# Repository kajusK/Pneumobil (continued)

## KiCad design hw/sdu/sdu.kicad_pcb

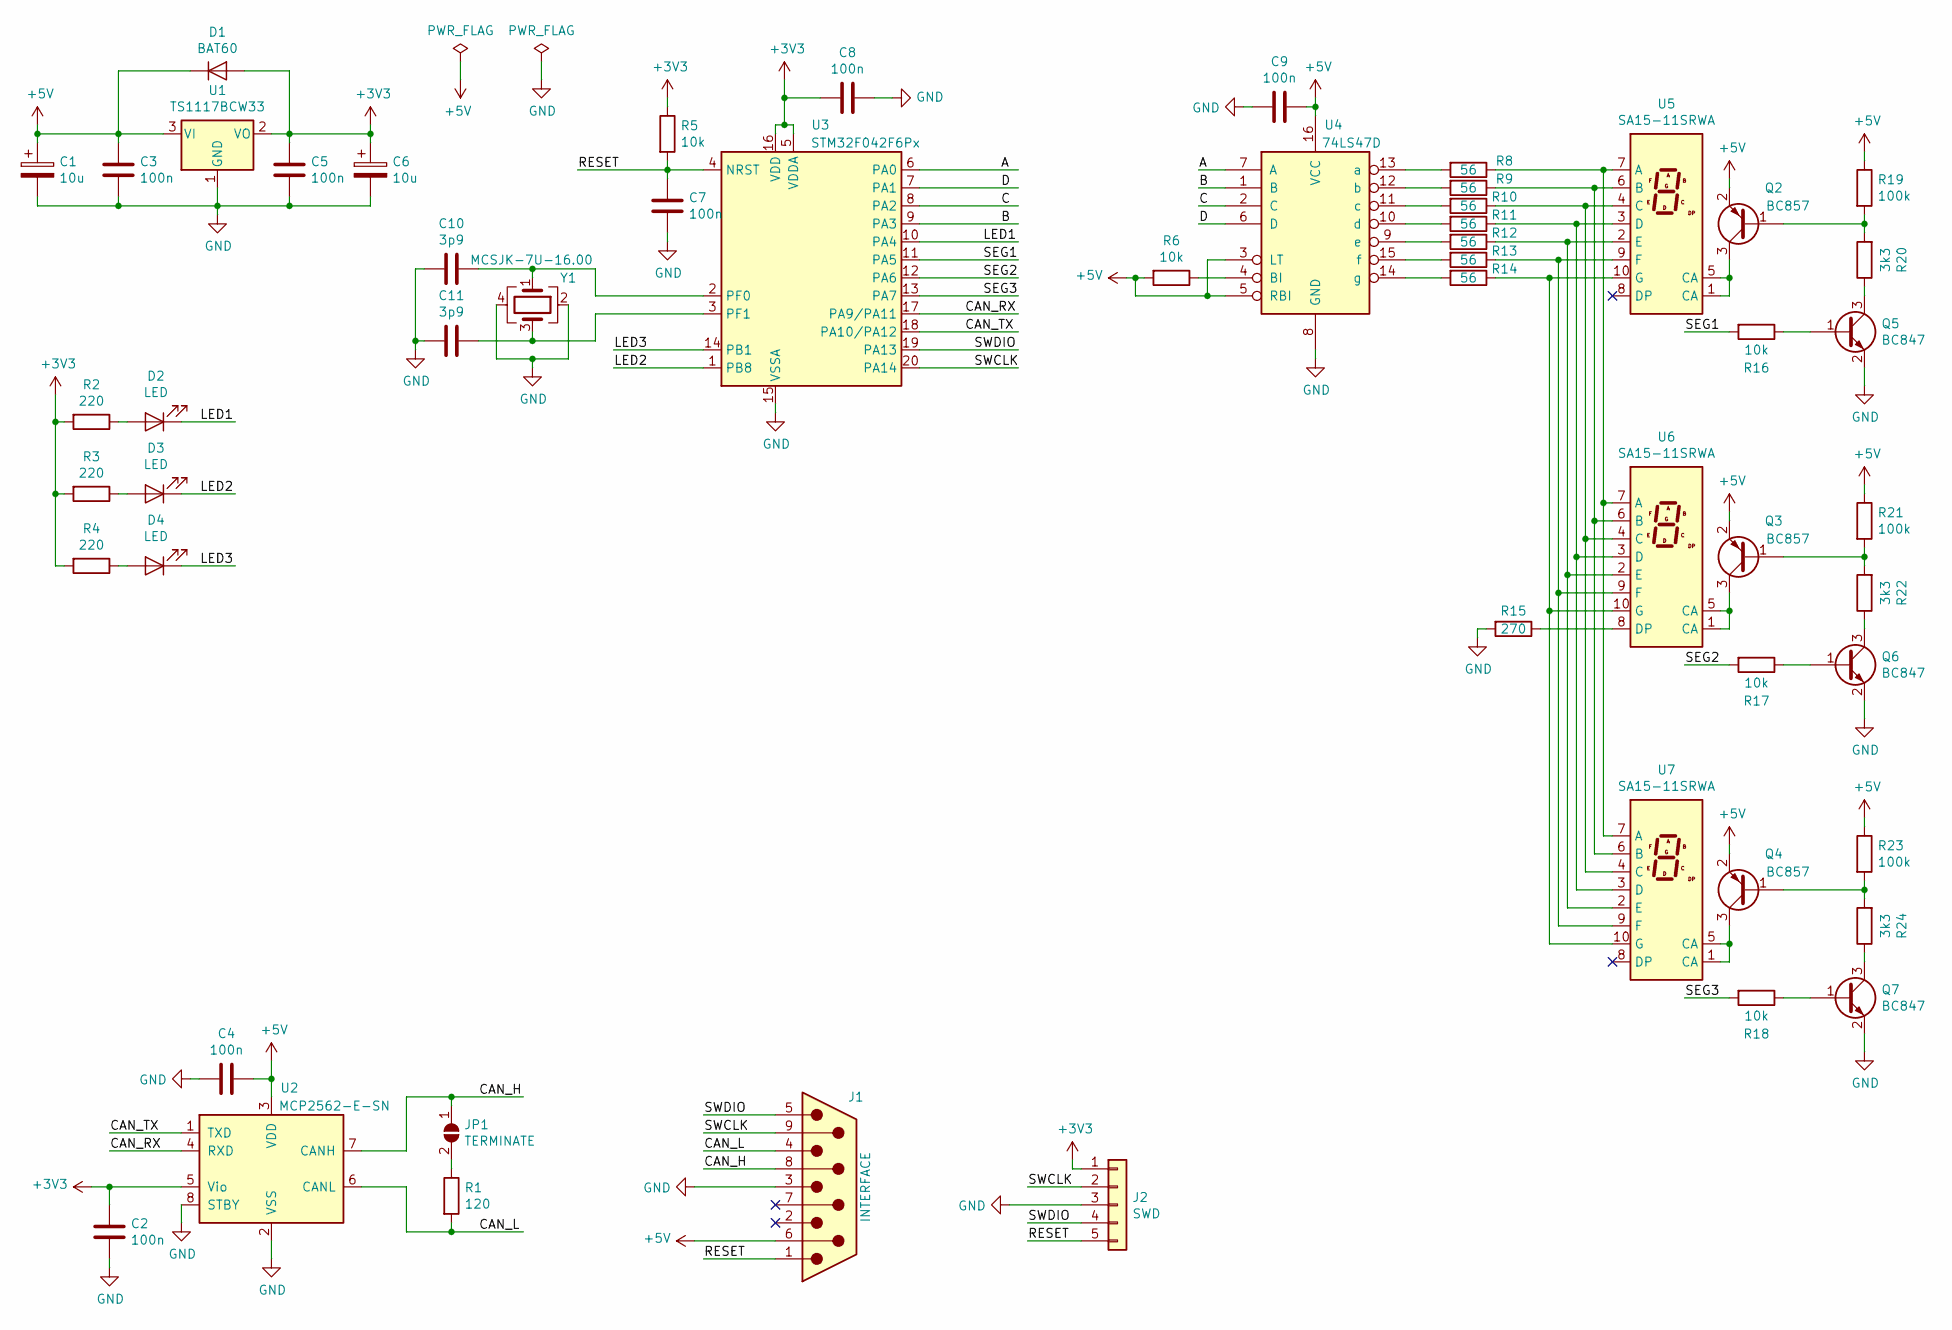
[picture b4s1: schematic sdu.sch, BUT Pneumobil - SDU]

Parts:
C1, C6: 10u; C_0805_2012Metric
C2, C3, C4, C5, C7, C8, C9: 100n; C_0805_2012Metric
C10, C11: 3p9; C_0805_2012Metric
D1: BAT60; D_SOD-323
D2, D3, D4: LED; LED_D5.0mm
J1: INTERFACE; DSUB-9_Female_Vertical_P2.77x2.84mm_MountingHoles
J2: SWD; PinHeader_1x05_P2.54mm_Horizontal
JP1: TERMINATE; SolderJumper-2_P1.3mm_Open_TrianglePad1.0x1.5mm
Q2, Q3, Q4: BC857; SOT-23
Q5, Q6, Q7: BC847; SOT-23
R1: 120; R_0805_2012Metric
R2, R3, R4: 220; R_0805_2012Metric
R5, R6, R16, R17, R18: 10k; R_0805_2012Metric
R8, R9, R10, R11, R12, R13, R14: 56; R_0805_2012Metric
R15: 270; R_0805_2012Metric
R19, R21, R23: 100k; R_0805_2012Metric
R20, R22, R24: 3k3; R_0805_2012Metric
U1: TS1117BCW33; SOT-223-3_TabPin2
U2: MCP2562-E-SN; SOIC-8_3.9x4.9mm_P1.27mm
U3: STM32F042F6Px; TSSOP-20_4.4x6.5mm_P0.65mm
U4: 74LS47D; SOIC-16_3.9x9.9mm_P1.27mm
U5, U6, U7: SA15-11SRWA; SA15-11
Y1: MCSJK-7U-16.00; Crystal_SMD_3225-4Pin_3.2x2.5mm

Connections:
+3V3: C2.1, C5.1, C6.1, C8.2, D1.2 (A), J2.1, R2.2, R3.2, R4.2, R5.1, U1.2 (VO), U2.5 (Vio), U3.5 (VDDA), U3.16 (VDD)
+5V: C1.1, C3.1, C4.1, C9.1, D1.1 (K), J1.6, Q2.2 (E), Q3.2 (E), Q4.2 (E), R6.2, R19.1, R21.1, R23.1, U1.3 (VI), U2.3 (VDD), U4.3 (LT), U4.5 (RBI), U4.16 (VCC)
/A: U3.6 (PA0), U4.7 (A)
/B: U3.9 (PA3), U4.1 (B)
/C: U3.8 (PA2), U4.2 (C)
/CAN_H: J1.8, JP1.1 (A), U2.7 (CANH)
/CAN_L: J1.4, R1.2, U2.6 (CANL)
/CAN_RX: U2.4 (RXD), U3.17 (PA9/PA11)
/CAN_TX: U2.1 (TXD), U3.18 (PA10/PA12)
/D: U3.7 (PA1), U4.6 (D)
/LED1: D2.1 (K), U3.10 (PA4)
/LED2: D3.1 (K), U3.1 (PB8)
/LED3: D4.1 (K), U3.14 (PB1)
/RESET: C7.1, J1.1, J2.5, R5.2, U3.4 (NRST)
/SEG1: R16.2, U3.11 (PA5)
/SEG2: R17.2, U3.12 (PA6)
/SEG3: R18.2, U3.13 (PA7)
/SWCLK: J1.9, J2.2, U3.20 (PA14)
/SWDIO: J1.5, J2.4, U3.19 (PA13)
GND: C1.2, C2.2, C3.2, C4.2, C5.2, C6.2, C7.2, C8.1, C9.2, C10.2, C11.2, J1.3, J2.3, Q5.2 (E), Q6.2 (E), Q7.2 (E), R15.2, U1.1 (GND), U2.2 (VSS), U2.8 (STBY), U3.15 (VSSA), U4.8 (GND), Y1.2, Y1.4
unnamed: C10.1, U3.2 (PF0), Y1.1
unnamed: C11.1, U3.3 (PF1), Y1.3
unnamed: D2.2 (A), R2.1
unnamed: D3.2 (A), R3.1
unnamed: D4.2 (A), R4.1
unnamed: JP1.2 (B), R1.1
unnamed: Q2.1 (B), R19.2, R20.2
unnamed: Q2.3 (C), U5.1 (CA), U5.5 (CA)
unnamed: Q3.1 (B), R21.2, R22.2
unnamed: Q3.3 (C), U6.1 (CA), U6.5 (CA)
unnamed: Q4.1 (B), R23.2, R24.2
unnamed: Q4.3 (C), U7.1 (CA), U7.5 (CA)
unnamed: Q5.1 (B), R16.1
unnamed: Q5.3 (C), R20.1
unnamed: Q6.1 (B), R17.1
unnamed: Q6.3 (C), R22.1
unnamed: Q7.1 (B), R18.1
unnamed: Q7.3 (C), R24.1
unnamed: R6.1, U4.4 (BI)
unnamed: R8.1, U5.7 (A), U6.7 (A), U7.7 (A)
unnamed: R8.2, U4.13 (a)
unnamed: R9.1, U5.6 (B), U6.6 (B), U7.6 (B)
unnamed: R9.2, U4.12 (b)
unnamed: R10.1, U5.4 (C), U6.4 (C), U7.4 (C)
unnamed: R10.2, U4.11 (c)
unnamed: R11.1, U5.3 (D), U6.3 (D), U7.3 (D)
unnamed: R11.2, U4.10 (d)
unnamed: R12.1, U5.2 (E), U6.2 (E), U7.2 (E)
unnamed: R12.2, U4.9 (e)
unnamed: R13.1, U5.9 (F), U6.9 (F), U7.9 (F)
unnamed: R13.2, U4.15 (f)
unnamed: R14.1, U5.10 (G), U6.10 (G), U7.10 (G)
unnamed: R14.2, U4.14 (g)
unnamed: R15.1, U6.8 (DP)

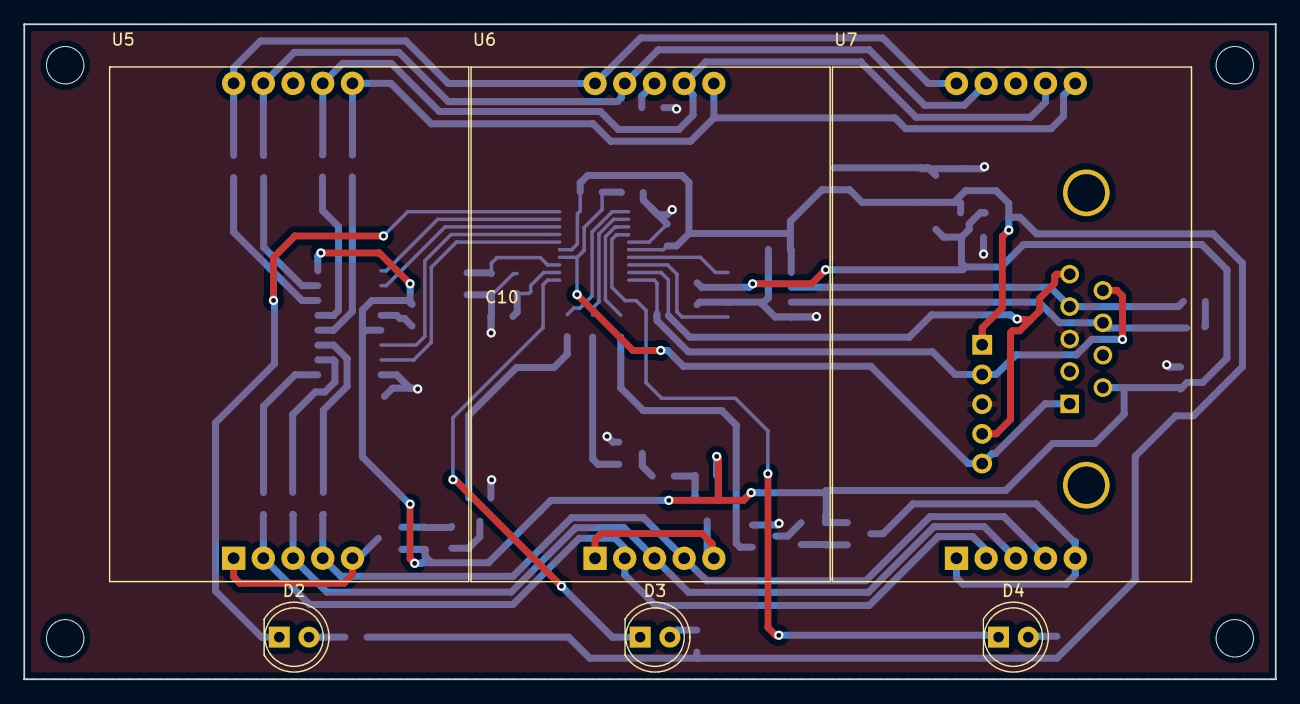
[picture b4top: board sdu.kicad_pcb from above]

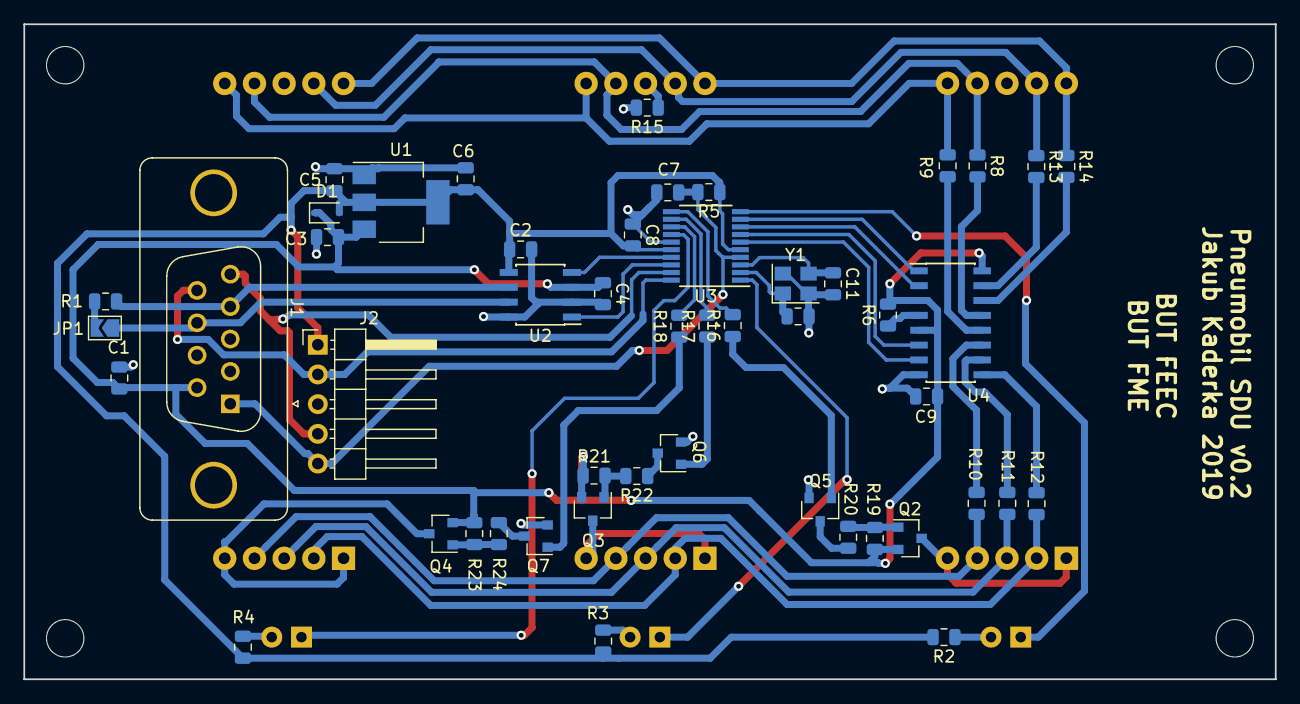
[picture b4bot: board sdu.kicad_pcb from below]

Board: 2 copper layers, 107.0 x 56.0 mm, 55 parts (49 on the bottom side), 54 nets.

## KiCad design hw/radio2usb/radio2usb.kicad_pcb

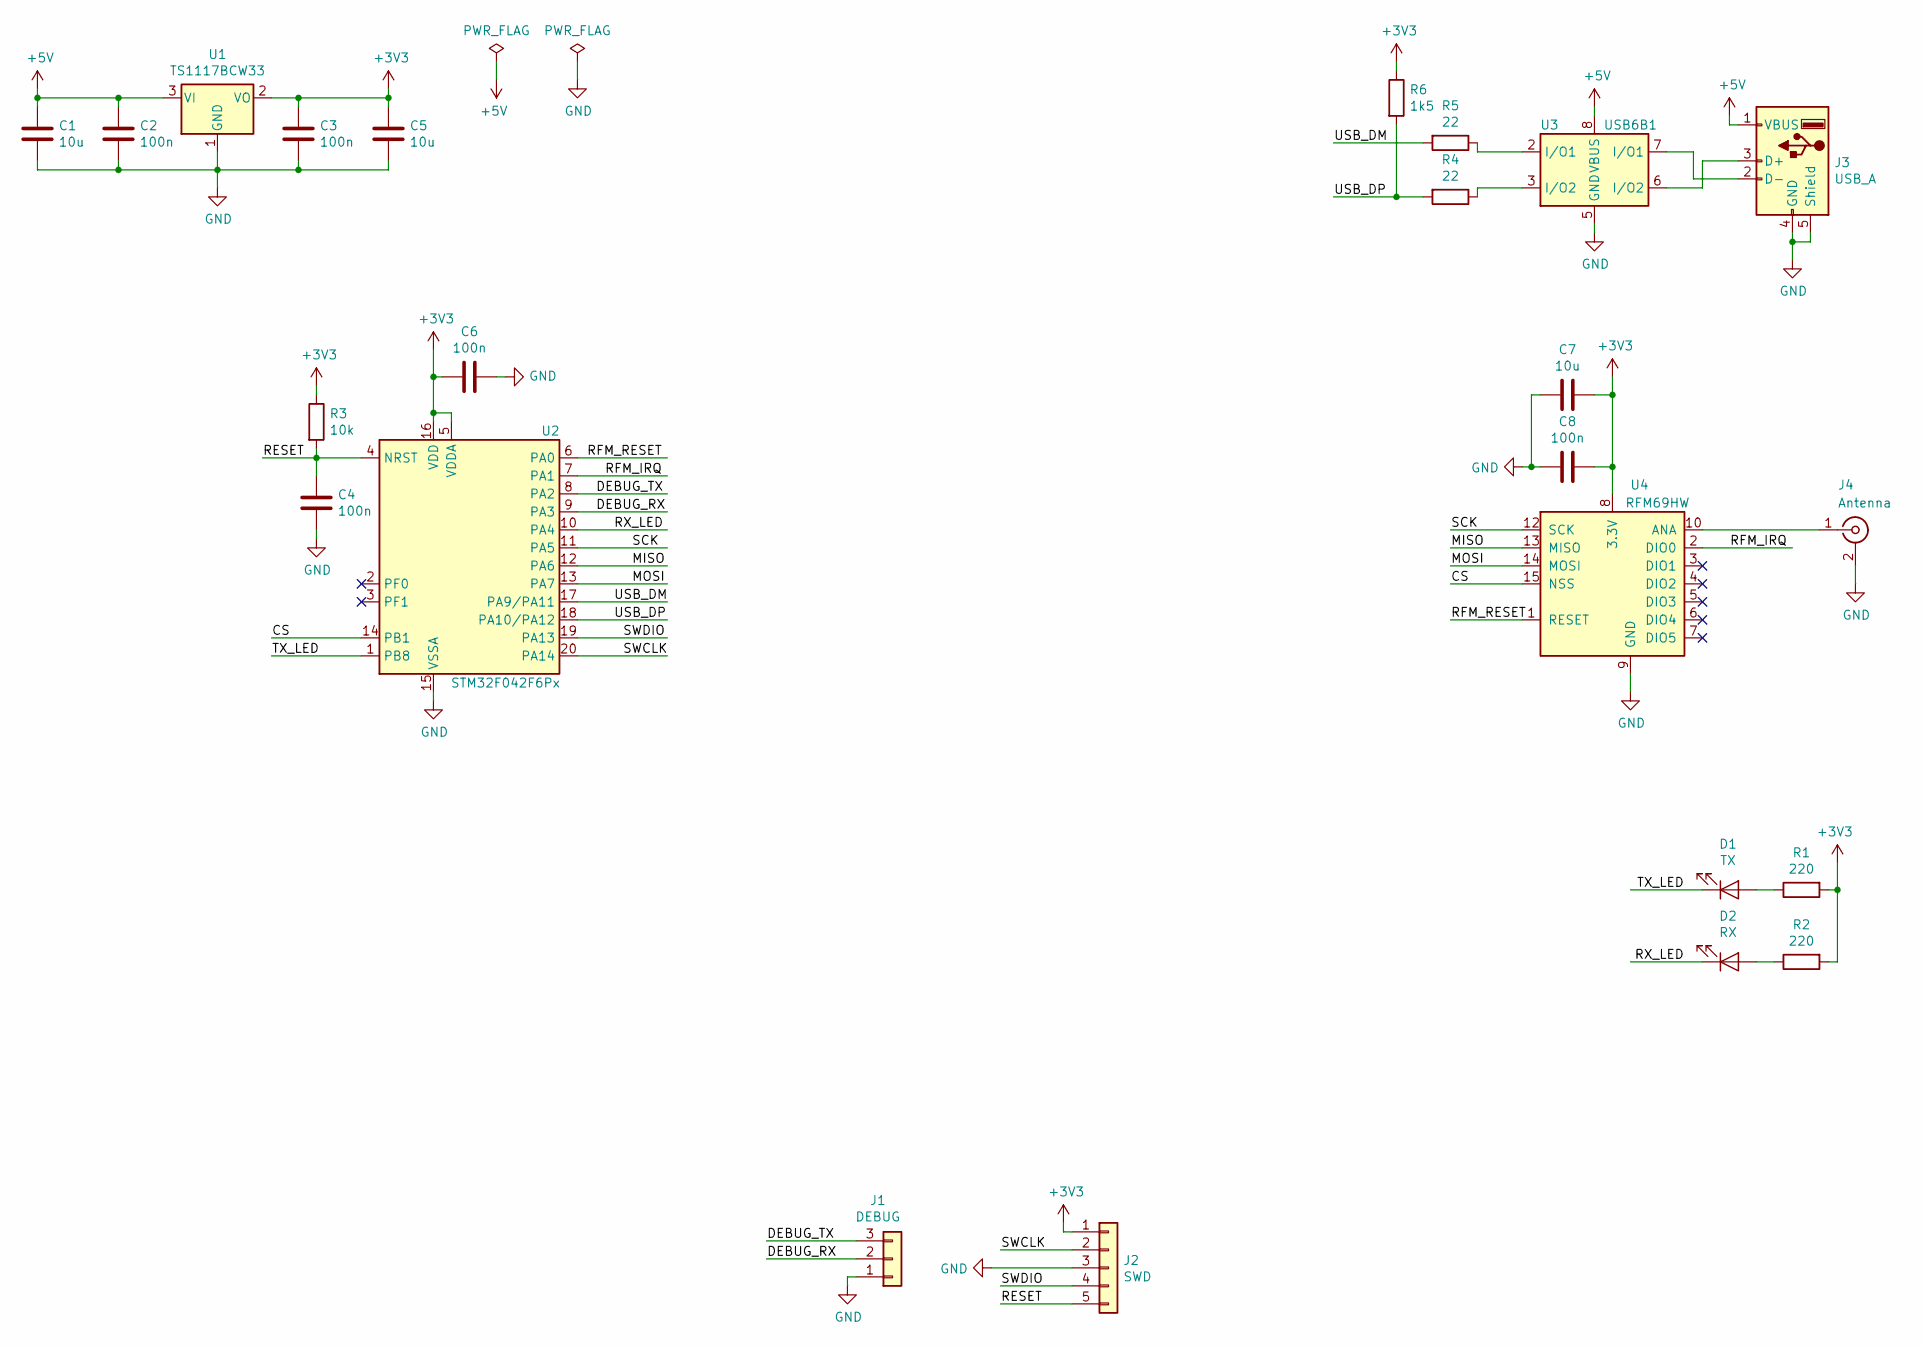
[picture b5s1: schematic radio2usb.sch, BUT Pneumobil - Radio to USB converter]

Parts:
C1, C5, C7: 10u; C_0805_2012Metric
C2, C3, C4, C6, C8: 100n; C_0805_2012Metric
D1: TX; LED_1206_3216Metric
D2: RX; LED_1206_3216Metric
J1: DEBUG; PinHeader_1x03_P2.54mm_Vertical
J2: SWD; PinHeader_1x05_P2.54mm_Vertical
J3: USB_A; USB_A_CNCTech_1001-011-01101_Horizontal
J4: Antenna; SMA_Amphenol_132134-11_Vertical
R1, R2: 220; R_0805_2012Metric
R3: 10k; R_0805_2012Metric
R4, R5: 22; R_0805_2012Metric
R6: 1k5; R_0805_2012Metric
U1: TS1117BCW33; SOT-223-3_TabPin2
U2: STM32F042F6Px; TSSOP-20_4.4x6.5mm_P0.65mm
U3: USB6B1; SOIC-8_3.9x4.9mm_P1.27mm
U4: RFM69HW; HOPERF_RFM69HW

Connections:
+3V3: C3.1, C5.1, C6.2, C7.1, C8.1, J2.1, R1.2, R2.2, R3.1, R6.1, U1.2 (VO), U2.5 (VDDA), U2.16 (VDD), U4.8 (3.3V)
+5V: C1.1, C2.1, J3.1 (VBUS), U1.3 (VI), U3.1 (VBUS), U3.8 (VBUS)
/CS: U2.14 (PB1), U4.15 (NSS)
/DEBUG_RX: J1.2, U2.9 (PA3)
/DEBUG_TX: J1.3, U2.8 (PA2)
/MISO: U2.12 (PA6), U4.13 (MISO)
/MOSI: U2.13 (PA7), U4.14 (MOSI)
/RESET: C4.1, J2.5, R3.2, U2.4 (NRST)
/RFM_IRQ: U2.7 (PA1), U4.2 (DIO0)
/RFM_RESET: U2.6 (PA0), U4.1 (RESET)
/RX_LED: D2.1 (K), U2.10 (PA4)
/SCK: U2.11 (PA5), U4.12 (SCK)
/SWCLK: J2.2, U2.20 (PA14)
/SWDIO: J2.4, U2.19 (PA13)
/TX_LED: D1.1 (K), U2.1 (PB8)
/USB_DM: R5.2, U2.17 (PA9/PA11)
/USB_DP: R4.2, R6.2, U2.18 (PA10/PA12)
GND: C1.2, C2.2, C3.2, C4.2, C5.2, C6.1, C7.2, C8.2, J1.1, J2.3, J3.4 (GND), J3.5 (Shield), J4.2 (Ext), U1.1 (GND), U2.15 (VSSA), U3.4 (GND), U3.5 (GND), U4.9 (GND), U4.11 (GND)
unnamed: D1.2 (A), R1.1
unnamed: D2.2 (A), R2.1
unnamed: J3.2 (D-), U3.7 (I/O1)
unnamed: J3.3 (D+), U3.6 (I/O2)
unnamed: J4.1 (In), U4.10 (ANA)
unnamed: R4.1, U3.3 (I/O2)
unnamed: R5.1, U3.2 (I/O1)

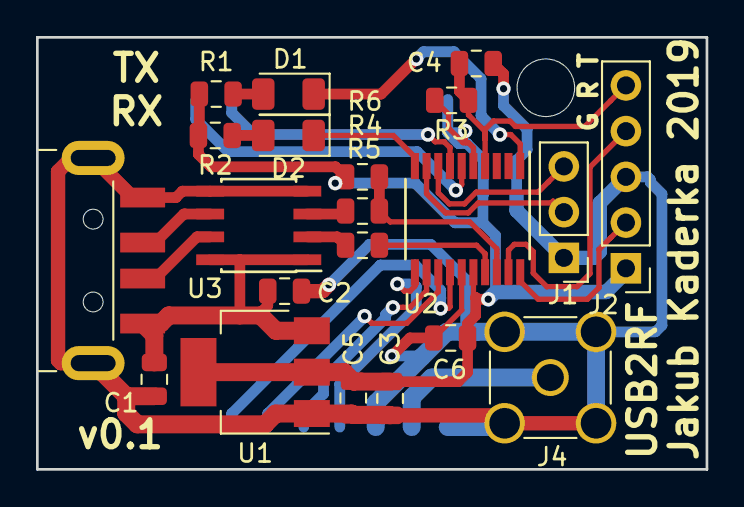
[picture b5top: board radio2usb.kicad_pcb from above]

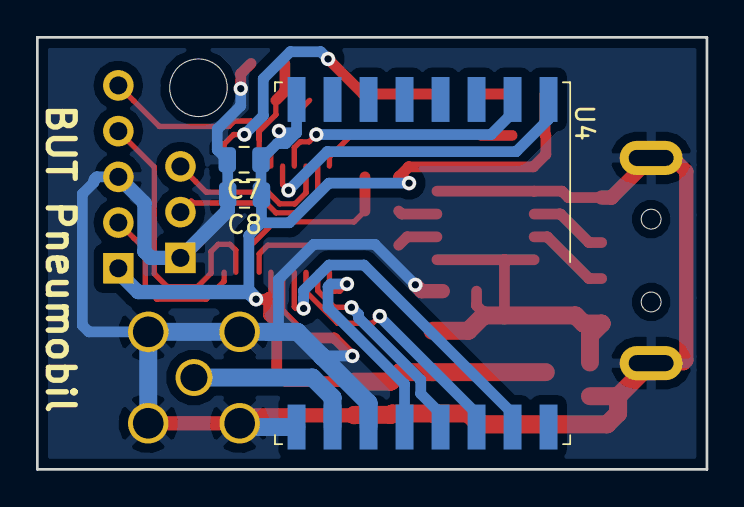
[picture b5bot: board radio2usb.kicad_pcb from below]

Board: 2 copper layers, 37.2 x 24.0 mm, 24 parts (3 on the bottom side), 25 nets.

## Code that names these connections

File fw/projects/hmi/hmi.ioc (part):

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Mcu.Name=STM32F412V(E-G)Tx
Mcu.Package=LQFP100
Mcu.UserName=STM32F412VETx
PA1.GPIOParameters=GPIO_Label
PA1.GPIO_Label=ADC_5V
PA1.Signal=ADCx_IN1
PA10.GPIOParameters=GPIO_Label
PA10.GPIO_Label=GPS_RXD
PA10.Mode=Asynchronous
PA10.Signal=USART1_RX
PA11.Mode=Host_Only
PA11.Signal=USB_OTG_FS_DM
PA12.Mode=Host_Only
PA12.Signal=USB_OTG_FS_DP
PA13.Mode=Serial_Wire
PA13.Signal=SYS_JTMS-SWDIO
PA14.Mode=Serial_Wire
PA14.Signal=SYS_JTCK-SWCLK
PA15.GPIOParameters=GPIO_Label
PA15.GPIO_Label=SD_DETECT
PA15.Signal=GPIO_Input
PA2.GPIOParameters=GPIO_Label
PA2.GPIO_Label=DEBUG_TXD
PA2.Mode=Asynchronous
PA2.Signal=USART2_TX
PA3.GPIOParameters=GPIO_Label
PA3.GPIO_Label=DEBUG_RXD
PA3.Mode=Asynchronous
PA3.Signal=USART2_RX
PA4.GPIOParameters=PinState,GPIO_Label
PA4.GPIO_Label=LED_USER
PA4.PinState=GPIO_PIN_SET
PA4.Signal=GPIO_Output
PA5.GPIOParameters=PinState,GPIO_Label
PA5.GPIO_Label=LED_SYS_ACTIVE
PA5.PinState=GPIO_PIN_SET
PA5.Signal=GPIO_Output
PA7.GPIOParameters=GPIO_Label
PA7.GPIO_Label=BTL1
PA7.Signal=GPIO_Input
PA8.GPIOParameters=GPIO_Speed,PinState,GPIO_Label
PA8.GPIO_Label=BME_CS
PA8.GPIO_Speed=GPIO_SPEED_FREQ_HIGH
PA8.PinState=GPIO_PIN_SET
PA8.Signal=GPIO_Output
PA9.GPIOParameters=GPIO_Label
PA9.GPIO_Label=GPS_TXD
PA9.Mode=Asynchronous
PA9.Signal=USART1_TX
PB0.GPIOParameters=GPIO_Label
PB0.GPIO_Label=BTR1
PB0.Signal=GPIO_Input
PB1.GPIOParameters=GPIO_Label
PB1.GPIO_Label=BTR2
PB1.Signal=GPIO_Input
PB12.GPIOParameters=GPIO_Speed,PinState,GPIO_Label
PB12.GPIO_Label=LCD_T_CS
PB12.GPIO_Speed=GPIO_SPEED_FREQ_HIGH
PB12.PinState=GPIO_PIN_SET
PB12.Signal=GPIO_Output
PB13.GPIOParameters=GPIO_Label
PB13.GPIO_Label=DISP_SCK
PB13.Mode=Full_Duplex_Master
PB13.Signal=SPI2_SCK
PB14.GPIOParameters=GPIO_Label
PB14.GPIO_Label=DISP_MISO
PB14.Mode=Full_Duplex_Master
PB14.Signal=SPI2_MISO
PB15.GPIOParameters=GPIO_Label
PB15.GPIO_Label=DISP_MOSI
PB15.Mode=Full_Duplex_Master
PB15.Signal=SPI2_MOSI
PB2.GPIOParameters=GPIO_Label
PB2.GPIO_Label=BTR3
PB2.Signal=GPIO_Input
PB4.GPIOParameters=GPIO_Label
PB4.GPIO_Label=BUZZER
PB4.Signal=S_TIM3_CH1
PB6.Mode=I2C
PB6.Signal=I2C1_SCL
PB7.Mode=I2C
PB7.Signal=I2C1_SDA
PB8.GPIOParameters=GPIO_Label
PB8.GPIO_Label=CAN_TX
PB8.Mode=Master
PB8.Signal=CAN1_RX
PB9.GPIOParameters=GPIO_Label
PB9.GPIO_Label=CAN_RX
PB9.Mode=Master
PB9.Signal=CAN1_TX
PC10.Mode=SD_4_bits_Wide_bus
PC10.Signal=SDIO_D2
PC11.Mode=SD_4_bits_Wide_bus
PC11.Signal=SDIO_D3
PC12.Mode=SD_4_bits_Wide_bus
PC12.Signal=SDIO_CK
PC14-OSC32_IN.Mode=LSE-External-Oscillator
PC14-OSC32_IN.Signal=RCC_OSC32_IN
PC15-OSC32_OUT.Mode=LSE-External-Oscillator
PC15-OSC32_OUT.Signal=RCC_OSC32_OUT
PC4.GPIOParameters=GPIO_Label
PC4.GPIO_Label=BTL2
PC4.Signal=GPIO_Input
PC5.GPIOParameters=GPIO_Label
PC5.GPIO_Label=BTL3
PC5.Signal=GPIO_Input
PC6.GPIOParameters=GPIO_Label
PC6.GPIO_Label=LCD_REST
PC6.Signal=GPIO_Output
PC7.GPIOParameters=GPIO_Speed,PinState,GPIO_Label
PC7.GPIO_Label=LCD_SD_CS
PC7.GPIO_Speed=GPIO_SPEED_FREQ_HIGH
PC7.PinState=GPIO_PIN_SET
PC7.Signal=GPIO_Output
PC8.Mode=SD_4_bits_Wide_bus
PC8.Signal=SDIO_D0
PC9.Mode=SD_4_bits_Wide_bus
PC9.Signal=SDIO_D1
PD0.Signal=FSMC_D2_DA2
PD1.Signal=FSMC_D3_DA3
PD10.Signal=FSMC_D15_DA15
PD11.GPIOParameters=GPIO_Label
PD11.GPIO_Label=LCD_T_IRQ
PD11.Signal=GPIO_Input
PD12.GPIOParameters=GPIO_Speed,PinState,GPIO_Label
PD12.GPIO_Label=LCD_F_CS
PD12.GPIO_Speed=GPIO_SPEED_FREQ_HIGH
PD12.PinState=GPIO_PIN_SET
PD12.Signal=GPIO_Output
PD13.GPIOParameters=GPIO_Label
PD13.GPIO_Label=LCD_RS
PD13.Signal=FSMC_A18
PD14.Signal=FSMC_D0_DA0
PD15.Signal=FSMC_D1_DA1
PD2.Mode=SD_4_bits_Wide_bus
PD2.Signal=SDIO_CMD
PD4.Signal=FSMC_NOE
PD5.Signal=FSMC_NWE
PD7.GPIOParameters=GPIO_Label
PD7.GPIO_Label=LCD_CS
PD7.Mode=NorPsramChipSelect1_1
PD7.Signal=FSMC_NE1
PD8.Signal=FSMC_D13_DA13
PD9.Signal=FSMC_D14_DA14
PE1.GPIOParameters=GPIO_Label
PE1.GPIO_Label=RFM_RESET
PE1.Signal=GPIO_Output
PE10.Signal=FSMC_D7_DA7
PE11.Signal=FSMC_D8_DA8
PE12.Signal=FSMC_D9_DA9
PE13.Signal=FSMC_D10_DA10
PE14.Signal=FSMC_D11_DA11
PE15.Signal=FSMC_D12_DA12
PE2.GPIOParameters=GPIO_Label
PE2.GPIO_Label=COMM_SCK
PE2.Mode=Full_Duplex_Master
PE2.Signal=SPI4_SCK
PE3.GPIOParameters=GPIO_Speed,PinState,GPIO_Label
PE3.GPIO_Label=RFM_CS
PE3.GPIO_Speed=GPIO_SPEED_FREQ_HIGH
PE3.PinState=GPIO_PIN_SET
PE3.Signal=GPIO_Output
PE4.GPIOParameters=GPIO_Label
PE4.GPIO_Label=RFM_IRQ
PE4.Signal=GPIO_Input
PE5.GPIOParameters=GPIO_Label
PE5.GPIO_Label=COMM_MISO
PE5.Mode=Full_Duplex_Master
PE5.Signal=SPI4_MISO
PE6.GPIOParameters=GPIO_Label
PE6.GPIO_Label=COMM_MOSI
PE6.Mode=Full_Duplex_Master
PE6.Signal=SPI4_MOSI
PE7.Signal=FSMC_D4_DA4
PE8.Signal=FSMC_D5_DA5
PE9.Signal=FSMC_D6_DA6
PH0\ -\ OSC_IN.Mode=HSE-External-Oscillator
PH0\ -\ OSC_IN.Signal=RCC_OSC_IN
PH1\ -\ OSC_OUT.Mode=HSE-External-Oscillator
PH1\ -\ OSC_OUT.Signal=RCC_OSC_OUT
RCC.HSE_VALUE=12000000
RCC.SYSCLKFreq_VALUE=96000000
RCC.SYSCLKSource=RCC_SYSCLKSOURCE_PLLCLK
board=custom

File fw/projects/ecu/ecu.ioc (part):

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Mcu.Name=STM32F072R(8-B)Tx
Mcu.Package=LQFP64
Mcu.UserName=STM32F072RBTx
PA0.GPIOParameters=GPIO_Label
PA0.GPIO_Label=EXPANSION_TX
PA0.Mode=Asynchronous
PA0.Signal=USART4_TX
PA1.GPIOParameters=GPIO_Label
PA1.GPIO_Label=EXPANSION_RX
PA1.Mode=Asynchronous
PA1.Signal=USART4_RX
PA10.GPIOParameters=GPIO_Label
PA10.GPIO_Label=DEBUG_RXD
PA10.Mode=Asynchronous
PA10.Signal=USART1_RX
PA11.Mode=Device
PA11.Signal=USB_DM
PA12.Mode=Device
PA12.Signal=USB_DP
PA13.Mode=Serial_Wire
PA13.Signal=SYS_SWDIO
PA14.Mode=Serial_Wire
PA14.Signal=SYS_SWCLK
PA15.GPIOParameters=GPIO_Label
PA15.GPIO_Label=VALVE_B2A
PA15.Signal=GPIO_Output
PA2.GPIOParameters=GPIO_Label
PA2.GPIO_Label=WIRE1
PA2.Signal=GPIO_Input
PA3.GPIOParameters=GPIO_Label
PA3.GPIO_Label=OUT1
PA3.Signal=GPIO_Output
PA4.GPIOParameters=GPIO_Label
PA4.GPIO_Label=CUR_LOOP_REF
PA4.Signal=COMP_DAC1_group
PA5.GPIOParameters=GPIO_Label
PA5.GPIO_Label=PRESSURE_6
PA5.Mode=IN5
PA5.Signal=ADC_IN5
PA6.GPIOParameters=GPIO_Label
PA6.GPIO_Label=PRESSURE_5
PA6.Mode=IN6
PA6.Signal=ADC_IN6
PA7.GPIOParameters=GPIO_Label
PA7.GPIO_Label=PRESSURE_4
PA7.Mode=IN7
PA7.Signal=ADC_IN7
PA8.GPIOParameters=GPIO_Label
PA8.GPIO_Label=SPEED_CNT
PA8.Signal=S_TIM1_CH1
PA9.GPIOParameters=GPIO_Label
PA9.GPIO_Label=DEBUG_TXD
PA9.Mode=Asynchronous
PA9.Signal=USART1_TX
PB0.GPIOParameters=GPIO_Label
PB0.GPIO_Label=PRESSURE_1
PB0.Mode=IN8
PB0.Signal=ADC_IN8
PB1.GPIOParameters=GPIO_Label
PB1.GPIO_Label=BRAKE
PB1.Signal=GPIO_Input
PB10.GPIOParameters=GPIO_Label
PB10.GPIO_Label=ENDSTOP_B2
PB10.Signal=GPIO_Input
PB11.GPIOParameters=GPIO_Label
PB11.GPIO_Label=ENDSTOP_B1
PB11.Signal=GPIO_Input
PB12.GPIOParameters=GPIO_Label
PB12.GPIO_Label=ENDSTOP_F2
PB12.Signal=GPIO_Input
PB13.GPIOParameters=GPIO_Label
PB13.GPIO_Label=ENDSTOP_F1
PB13.Signal=GPIO_Input
PB14.GPIOParameters=GPIO_Speed,PinState,GPIO_PuPd,GPIO_Label,GPIO_ModeDefaultOutputPP
PB14.GPIO_Label=VALVE_F1A
PB14.GPIO_ModeDefaultOutputPP=GPIO_MODE_OUTPUT_PP
PB14.GPIO_PuPd=GPIO_NOPULL
PB14.GPIO_Speed=GPIO_SPEED_FREQ_LOW
PB14.PinState=GPIO_PIN_RESET
PB14.Signal=GPIO_Output
PB15.GPIOParameters=GPIO_Speed,PinState,GPIO_PuPd,GPIO_Label,GPIO_ModeDefaultOutputPP
PB15.GPIO_Label=VALVE_F1B
PB15.GPIO_ModeDefaultOutputPP=GPIO_MODE_OUTPUT_PP
PB15.GPIO_PuPd=GPIO_NOPULL
PB15.GPIO_Speed=GPIO_SPEED_FREQ_LOW
PB15.PinState=GPIO_PIN_RESET
PB15.Signal=GPIO_Output
PB2.GPIOParameters=GPIO_Label
PB2.GPIO_Label=THROTTLE
PB2.Signal=GPIO_Input
PB3.GPIOParameters=GPIO_Label
PB3.GPIO_Label=GEARBOX_1
PB3.Signal=GPIO_Input
PB4.GPIOParameters=GPIO_Label
PB4.GPIO_Label=ROT_ENC_A
PB4.Signal=S_TIM3_CH1
PB5.GPIOParameters=GPIO_Label
PB5.GPIO_Label=ROT_ENC_B
PB5.Signal=S_TIM3_CH2
PB6.Mode=I2C
PB6.Signal=I2C1_SCL
PB7.Mode=I2C
PB7.Signal=I2C1_SDA
PB8.Mode=Master
PB8.Signal=CAN_RX
PB9.Mode=Master
PB9.Signal=CAN_TX
PC0.GPIOParameters=GPIO_Label
PC0.GPIO_Label=BT_SHIFTING
PC0.Signal=GPIO_Input
PC1.GPIOParameters=GPIO_Label
PC1.GPIO_Label=ADC_24V
PC1.Mode=IN11
PC1.Signal=ADC_IN11
PC10.GPIOParameters=GPIO_Label
PC10.GPIO_Label=VALVE_B2B
PC10.Signal=GPIO_Output
PC11.GPIOParameters=PinState,GPIO_Label
PC11.GPIO_Label=LED_SYS_ACTIVE
PC11.PinState=GPIO_PIN_SET
PC11.Signal=GPIO_Output
PC12.GPIOParameters=PinState,GPIO_Label
PC12.GPIO_Label=LED_USER
PC12.PinState=GPIO_PIN_SET
PC12.Signal=GPIO_Output
PC13.GPIOParameters=GPIO_Label
PC13.GPIO_Label=BT_HORN
PC13.Signal=GPIO_Input
PC14-OSC32_IN.GPIOParameters=GPIO_Label
PC14-OSC32_IN.GPIO_Label=BT_THROTTLE
PC14-OSC32_IN.Signal=GPIO_Input
PC15-OSC32_OUT.GPIOParameters=GPIO_Label
PC15-OSC32_OUT.GPIO_Label=BT_MODE
PC15-OSC32_OUT.Signal=GPIO_Input
PC2.GPIOParameters=GPIO_Label
PC2.GPIO_Label=ADC_12V
PC2.Mode=IN12
PC2.Signal=ADC_IN12
PC3.GPIOParameters=GPIO_Label
PC3.GPIO_Label=CUR_LOOP_IN
PC3.Mode=IN13
PC3.Signal=ADC_IN13
PC4.GPIOParameters=GPIO_Label
PC4.GPIO_Label=PRESSURE_3
PC4.Mode=IN14
PC4.Signal=ADC_IN14
PC5.GPIOParameters=GPIO_Label
PC5.GPIO_Label=PRESSURE_2
PC5.Mode=IN15
PC5.Signal=ADC_IN15
PC6.GPIOParameters=GPIO_Label
PC6.GPIO_Label=VALVE_F2A
PC6.Signal=GPIO_Output
PC7.GPIOParameters=GPIO_Speed,PinState,GPIO_PuPd,GPIO_Label,GPIO_ModeDefaultOutputPP
PC7.GPIO_Label=VALVE_F2B
PC7.GPIO_ModeDefaultOutputPP=GPIO_MODE_OUTPUT_PP
PC7.GPIO_PuPd=GPIO_NOPULL
PC7.GPIO_Speed=GPIO_SPEED_FREQ_LOW
PC7.PinState=GPIO_PIN_RESET
PC7.Signal=GPIO_Output
PC8.GPIOParameters=GPIO_Speed,PinState,GPIO_PuPd,GPIO_Label,GPIO_ModeDefaultOutputPP
PC8.GPIO_Label=VALVE_B1A
PC8.GPIO_ModeDefaultOutputPP=GPIO_MODE_OUTPUT_PP
PC8.GPIO_PuPd=GPIO_NOPULL
PC8.GPIO_Speed=GPIO_SPEED_FREQ_LOW
PC8.PinState=GPIO_PIN_RESET
PC8.Signal=GPIO_Output
PC9.GPIOParameters=GPIO_Speed,PinState,GPIO_PuPd,GPIO_Label,GPIO_ModeDefaultOutputPP
PC9.GPIO_Label=VALVE_B1B
PC9.GPIO_ModeDefaultOutputPP=GPIO_MODE_OUTPUT_PP
PC9.GPIO_PuPd=GPIO_NOPULL
PC9.GPIO_Speed=GPIO_SPEED_FREQ_LOW
PC9.PinState=GPIO_PIN_RESET
PC9.Signal=GPIO_Output
PD2.GPIOParameters=GPIO_Label
PD2.GPIO_Label=OUT2
PD2.Signal=GPIO_Output
PF0-OSC_IN.Mode=HSE-External-Oscillator
PF0-OSC_IN.Signal=RCC_OSC_IN
PF1-OSC_OUT.Mode=HSE-External-Oscillator
PF1-OSC_OUT.Signal=RCC_OSC_OUT
RCC.HSE_VALUE=16000000
RCC.SYSCLKFreq_VALUE=48000000
RCC.SYSCLKSource=RCC_SYSCLKSOURCE_PLLCLK
board=custom

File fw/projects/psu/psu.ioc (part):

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Mcu.Name=STM32F042F6Px
Mcu.Package=TSSOP20
Mcu.UserName=STM32F042F6Px
PA0.GPIOParameters=GPIO_Label
PA0.GPIO_Label=U_B2
PA0.Mode=IN0
PA0.Signal=ADC_IN0
PA1.GPIOParameters=GPIO_Label
PA1.GPIO_Label=U_B1
PA1.Mode=IN1
PA1.Signal=ADC_IN1
PA11.Mode=Master
PA11.Signal=CAN_RX
PA12.Mode=Master
PA12.Signal=CAN_TX
PA13.Mode=Serial_Wire
PA13.Signal=SYS_SWDIO
PA14.Mode=Serial_Wire
PA14.Signal=SYS_SWCLK
PA2.GPIOParameters=GPIO_Label
PA2.GPIO_Label=I_24
PA2.Mode=IN2
PA2.Signal=ADC_IN2
PA3.GPIOParameters=GPIO_Label
PA3.GPIO_Label=I_BAT
PA3.Mode=IN3
PA3.Signal=ADC_IN3
PA4.GPIOParameters=GPIO_Label
PA4.GPIO_Label=I_12
PA4.Mode=IN4
PA4.Signal=ADC_IN4
PA5.GPIOParameters=GPIO_Label
PA5.GPIO_Label=U_12
PA5.Mode=IN5
PA5.Signal=ADC_IN5
PA6.GPIOParameters=GPIO_Label
PA6.GPIO_Label=U_5
PA6.Mode=IN6
PA6.Signal=ADC_IN6
PA7.GPIOParameters=GPIO_Label
PA7.GPIO_Label=I_5
PA7.Mode=IN7
PA7.Signal=ADC_IN7
PB1.GPIOParameters=PinState,GPIO_Label
PB1.GPIO_Label=LED_VOLTAGE
PB1.PinState=GPIO_PIN_SET
PB1.Signal=GPIO_Output
PB8.GPIOParameters=PinState,GPIO_Label
PB8.GPIO_Label=LED_CURRENT
PB8.PinState=GPIO_PIN_SET
PB8.Signal=GPIO_Output
PF0-OSC_IN.Mode=HSE-External-Oscillator
PF0-OSC_IN.Signal=RCC_OSC_IN
PF1-OSC_OUT.Mode=HSE-External-Oscillator
PF1-OSC_OUT.Signal=RCC_OSC_OUT
board=custom

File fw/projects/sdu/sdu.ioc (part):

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Mcu.Name=STM32F042F6Px
Mcu.Package=TSSOP20
Mcu.UserName=STM32F042F6Px
PA0.GPIOParameters=GPIO_Label
PA0.GPIO_Label=A
PA0.Signal=GPIO_Output
PA1.GPIOParameters=GPIO_Label
PA1.GPIO_Label=D
PA1.Signal=GPIO_Output
PA11.Mode=Master
PA11.Signal=CAN_RX
PA12.Mode=Master
PA12.Signal=CAN_TX
PA13.Mode=Serial_Wire
PA13.Signal=SYS_SWDIO
PA14.Mode=Serial_Wire
PA14.Signal=SYS_SWCLK
PA2.GPIOParameters=GPIO_Label
PA2.GPIO_Label=C
PA2.Signal=GPIO_Output
PA3.GPIOParameters=GPIO_Label
PA3.GPIO_Label=B
PA3.Signal=GPIO_Output
PA4.GPIOParameters=PinState,GPIO_Label
PA4.GPIO_Label=LED1
PA4.PinState=GPIO_PIN_SET
PA4.Signal=GPIO_Output
PA5.GPIOParameters=GPIO_Label
PA5.GPIO_Label=SEG1
PA5.Signal=GPIO_Output
PA6.GPIOParameters=GPIO_Label
PA6.GPIO_Label=SEG2
PA6.Signal=GPIO_Output
PA7.GPIOParameters=GPIO_Label
PA7.GPIO_Label=SEG3
PA7.Signal=GPIO_Output
PB1.GPIOParameters=PinState,GPIO_Label
PB1.GPIO_Label=LED3
PB1.PinState=GPIO_PIN_SET
PB1.Signal=GPIO_Output
PB8.GPIOParameters=PinState,GPIO_Label
PB8.GPIO_Label=LED2
PB8.PinState=GPIO_PIN_SET
PB8.Signal=GPIO_Output
PF0-OSC_IN.Mode=HSE-External-Oscillator
PF0-OSC_IN.Signal=RCC_OSC_IN
PF1-OSC_OUT.Mode=HSE-External-Oscillator
PF1-OSC_OUT.Signal=RCC_OSC_OUT
RCC.HSE_VALUE=16000000
RCC.SYSCLKFreq_VALUE=48000000
RCC.SYSCLKSource=RCC_SYSCLKSOURCE_PLLCLK
board=custom

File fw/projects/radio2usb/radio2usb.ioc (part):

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Mcu.Name=STM32F042F6Px
Mcu.Package=TSSOP20
Mcu.UserName=STM32F042F6Px
PA0.GPIOParameters=GPIO_Label
PA0.GPIO_Label=RFM_RESET
PA0.Signal=GPIO_Output
PA1.GPIOParameters=GPIO_Label
PA1.GPIO_Label=RFM_IRQ
PA1.Signal=GPXTI1
PA11.Mode=Device
PA11.Signal=USB_DM
PA12.Mode=Device
PA12.Signal=USB_DP
PA13.Mode=Serial_Wire
PA13.Signal=SYS_SWDIO
PA14.Mode=Serial_Wire
PA14.Signal=SYS_SWCLK
PA2.GPIOParameters=GPIO_Label
PA2.GPIO_Label=DEBUG_TX
PA2.Mode=Asynchronous
PA2.Signal=USART2_TX
PA3.GPIOParameters=GPIO_Label
PA3.GPIO_Label=DEBUG_RX
PA3.Mode=Asynchronous
PA3.Signal=USART2_RX
PA4.GPIOParameters=PinState,GPIO_Label
PA4.GPIO_Label=RX_LED
PA4.PinState=GPIO_PIN_SET
PA4.Signal=GPIO_Output
PA5.GPIOParameters=GPIO_Label
PA5.GPIO_Label=RF_SCK
PA5.Mode=Full_Duplex_Master
PA5.Signal=SPI1_SCK
PA6.GPIOParameters=GPIO_Label
PA6.GPIO_Label=RF_MISO
PA6.Mode=Full_Duplex_Master
PA6.Signal=SPI1_MISO
PA7.GPIOParameters=GPIO_Label
PA7.GPIO_Label=RF_MOSI
PA7.Mode=Full_Duplex_Master
PA7.Signal=SPI1_MOSI
PB1.GPIOParameters=GPIO_Label
PB1.GPIO_Label=RFM_CS
PB1.Signal=GPIO_Output
PB8.GPIOParameters=PinState,GPIO_Label
PB8.GPIO_Label=TX_LED
PB8.PinState=GPIO_PIN_SET
PB8.Signal=GPIO_Output
RCC.SYSCLKFreq_VALUE=48000000
RCC.SYSCLKSource=RCC_SYSCLKSOURCE_HSI48
board=custom

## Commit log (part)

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2018-08-01 Added unity and libopencm3 libraries
2018-09-03 Updated external repositories
2018-09-03 Initial working Makefile for Chibios in custom dir structure
2018-09-16 Added log module and tests
2018-09-16 Added naming conventions. board names and pneumatic components specs
2018-09-16 Renamed pneumatic to ECU (engine control unit)
2018-09-23 Added asserts
2018-09-23 Moved log unit test to modules directory
2018-09-23 Added initial draft of eeprom driver
2018-09-23 Added watchdog handling
2018-09-23 Added DAC driver
2018-09-23 Updated naming conventions
2018-09-25 Separated makefile into several files
2018-09-26 Added timing calculation for i2c
2018-09-26 Don't show verbose output during make
2018-09-27 Compile only unit tests
2018-09-27 Added crc 8 calculation
2018-09-28 Added communication layer draft
2018-09-28 Added mutex to uart link sending
2018-09-28 Generate board config from stm32cubemx project
2018-10-14 Added pcb for ECU
2018-10-15 Added ChibiOS-Contrib to ecu build - QEI hal
2018-10-16 Remade makefile and compile stuff for contrib repo
2018-10-19 Added config module with draft config_items
2018-10-19 Added assert tests to unit tests
2018-10-19 Generated gerbers for ECU
2018-10-19 Added common types definitions (avoid including ch.h in headers)
2018-10-19 Added buttons handling
2018-10-19 Build coverage for tests
2018-10-19 Set dac output in mv
2018-10-27 Added engine driver
2018-11-02 Updated few resistors/capacitors values on board
2018-11-25 Added schematics for all parts
2018-12-06 Added HMI and SDU boards
2018-12-10 Updated docs
2018-12-10 Don't wait for endstop hit in init
    When the piston len is known, just set encoder to middle of the length
    and return from init, during first cycle the correct value will be set
    once the endstop is hit.
2018-12-10 Fixed line endings
2018-12-10 Fixed doxygen group
2018-12-10 Added option to select port in makefile
2018-12-16 Added CAN link layer
2018-12-17 Fixed my ID generation
2018-12-20 Added doxygen generator
2018-12-20 Added note about types.h
2018-12-20 Added note about crc table generation
2018-12-20 Ignore coverage directory
2019-01-02 Added can driver and defines for joining two string for easier peripheral selection
2019-01-02 Added log source for drivers
2019-01-02 Abstracted the encoder interface
2019-01-02 Added speed counter driver
2019-01-02 Added adc driver
2019-01-03 Added generator script for config_items
2019-01-03 Added generator script for communication commands
2019-01-03 Generalized the uart device selection
2019-01-03 Added reading car state
2019-01-03 Added generated board file
2019-01-06 Renamed link to transport layer to match the iso osi definition
2019-01-08 Added draft of higher layers of communication stack
2019-01-13 Added storage module for saving config to eeprom
2019-01-13 Added generator of crc computation lookup tables
2019-01-13 Cleaned up the main for ecu
2019-01-13 Fixed can filtering
2019-01-13 Send destination addr to presentation layer
2019-01-13 Added automated log sending
2019-01-13 Moved few functions from presentation to application layer
2019-01-13 Added setting/getting log severity to comm
2019-01-18 Added can and I2C support for stm32f4xx
2019-01-18 Added HMI project
2019-01-27 Added forgotten i2c initialization
2019-01-28 Added handling of the card insertion and removal
2019-01-29 Added RTC driver
2019-01-29 Added hmi to log sources
2019-01-29 Use secure time conversion
2019-01-30 Added logging to sd card to hmi module
2019-01-30 Increased amount of can receive mailboxes to match amount of boards used
2019-01-30 Fixed incorrect length in sending packets and added mutex for session communication
2019-01-30 Added gearbox state and horn button to ecu_io
2019-01-30 Added reading piston position for external modules to ecu
2019-01-30 Fixed headers
2019-01-31 Added seters for several outputs
2019-01-31 Added separate module for ecu race selection
2019-01-31 Added few app layer comm functions
2019-01-31 Added forgotten config item
2019-01-31 Added race mode selection
2019-01-31 Added pneu parameters to comm
2019-01-31 Implemented switching race modes by button press
2019-01-31 Added draft for logging incomming messages
2019-02-04 Added uGFX driver
2019-02-05 Added mocks to ecu test
2019-02-05 Added float to config module
2019-02-05 Fixed generating the UINT values
2019-02-11 Fixed chibios hal drivers initialization (config must be static)
2019-02-11 Fixed resetting the LCD
2019-02-11 Fixed input type for LCD touch screen controller IRQ
2019-02-14 Migrated to the recetn chibios
2019-02-14 Updated to latest ugfx
2019-02-14 Fixed writing to eeprom
2019-02-14 Fixed adc
2019-02-14 Added timeout to can
2019-02-14 Switched optimizations back on - no optimizations were causing system tasks stack overflow,...
2019-02-14 Moved num to string conversion to log module
2019-02-14 Initial GUI
2019-02-16 Fixed config tests (app must be included after helpers for correct include order)
2019-02-16 Added external module logs
2019-02-16 Added test for external log messages
2019-02-16 Fixed test config items
2019-02-16 Added task for logging data to sd card
2019-02-16 Added config floats to comm module
2019-02-16 Updated config items generator
2019-02-16 Added SDU code draft
2019-02-16 Updated descriptions
2019-02-16 Regenerated config items
2019-02-16 Added SDU logic
2019-02-16 Added psu logic (and updated log sources)
2019-02-16 Added event handling to gui
2019-02-16 Added stack space to psu
2019-03-06 Fixed can baudrate calculation
2019-03-07 Fixed receiving broadcast messages
2019-03-07 Reinit adc on timeout (adc in locked state)
2019-03-07 Decreased can timeout to avoid blocking for too long in case the can is not connected
2019-03-07 Avoid blocking sender thread when the execution time is too long
2019-03-07 Updated clocks for ecu
2019-03-07 Fixed mutex not unlocked on data sending error
2019-03-07 Fixed reading status info
2019-03-07 Increased can and uart drivers stacks
2019-03-07 Fixed can SID format, fixed sending multipart messages
2019-03-08 Fixed can timing, disabled auto retry (limited to 3 tries)
2019-03-08 Fixed reading status data
2019-03-08 Fixed setting can filters
2019-03-08 Increased ecu buffer
2019-03-09 Added board for radio2usb converter
2019-03-10 Updated schematic to latest changes in usb protection ic
2019-03-11 Added crystal for all can equipped boards
2019-03-11 Show console on latest tab
2019-03-12 Fixed sdc driver stack overflow, fixed insertion callback not called
2019-03-12 Updated log strings
2019-03-12 Fixed logging overflows and data format
2019-03-12 Create new log file on mode switching
2019-03-13 Fixed printing flaots to log
2019-03-13 Fixed storage float writing and events processing
2019-03-13 Reduced stack size to fit memory
2019-03-13 Increased stack size
2019-03-17 Added content of setup screen
2019-03-17 Added debug screen content
2019-03-17 Added sd card status
2019-03-22 Renamed log sources for each module to common APP
2019-03-22 Removed dot as it's controlled in hw
2019-03-22 Fixed tests for can comm
2019-03-22 Removed config module from modules where it's not needed
2019-03-25 Save current mode to eeprom
2019-03-25 Updated SDU board
2019-03-27 Fixed endstop inversion
2019-03-28 Removed message on both endstop on (tons of messages will block other, more important)
2019-03-28 Updated ecu init logic
2019-03-28 Reduced resolution of encoder for lower counting frequency
2019-03-28 New stm32cube output
2019-03-28 Fixed comm cmd bit field order
2019-03-28 Fixed dry run printing
2019-03-28 Fixed adc conversion - depth must be 1 for single result buffer
2019-03-28 Initialize memory pool before starting log thread
2019-03-28 Updated comments
2019-03-28 Added polarity note to pinouts
2019-03-28 Open both valves to for venting out
2019-03-28 Add dual valves mode changing
2019-03-29 Valve direction control updated to match current connection
2019-03-29 Increased uart stack
2019-03-29 Fixed deadtime variable size
2019-03-29 Move to more distant end when changing from idle to move state
2019-04-02 Fixed values of few components on psu board
2019-04-02 Decreased amount of log message buffers for psu and sdu to fit limited RAM
2019-04-04 Made space around connectors screw for nut
2019-04-04 Generated gerbers for manufacturing
2019-04-10 Added driver for rfm69 modules
2019-04-11 Added build requirements
2019-04-18 Remad shared GPIO on STM32F042 to correct pin
2019-04-18 Added note about config option bits for stm32F042
2019-04-18 Added clock source synchronization for USB peripheral
2019-04-18 Updated clock settings on radio2usb to run from internal 48MHz crystall
2019-04-19 Fixed watchdog timing
2019-04-19 Updated PSU fw
2019-04-19 Fixed sdu
2019-04-19 Added compiler optimizations to project specific makefiles
2019-04-19 Fixed wdg not building for hmi
2019-04-19 Use on board crystall for psu, sdu and ecu
2019-04-19 Updated clock scheme in sdu stm32cubemx project
2019-04-19 Add end of string character to log msg sent over external comm
2019-04-19 Commented out gearbox2 as it's not present on the new board
2019-04-19 Send can data in same order the mailbox are filled
2019-04-20 Fixed ecu unit test to build
2019-04-20 Fixed direction select on throttle press
2019-04-20 Lock can using mutex when sending mutlipart message
2019-04-20 Increased port stack for ecu compiled with -O0
2019-04-20 display race time
2019-04-20 show module uptime instead of temperature
2019-04-20 Restart session semaphore before sending data to avoid the response miss
2019-04-20 Log must be initialized before comm for cases when log message arrives immediately after comm enable
2019-04-20 Fixed sending responses
2019-04-20 Fixed printing pct in status screen
2019-04-20 Added printing battery info to tabs header
2019-04-20 Added piston len reset button to debug screen (without logic behind yet)
2019-04-22 Fixed pin remmaping - moved to correct init function
2019-04-22 Added horn control to gui
2019-04-22 Fixed race logging
2019-04-22 Write race log only after log file has been created
2019-04-22 Added checking ecu timing for safety
2019-04-22 atollic bullshit
2019-04-23 Added reboot option
2019-04-23 Moved magic number verification to app layer where it belongs
2019-04-25 Added on select event to screens, added reading and resetting piston len
2019-04-25 Load pneu params on screen select
2019-04-25 Fixed current measurement by psu
2019-04-25 Initialize log before comm
2019-04-25 Unified include guards
2019-04-25 Enabled watchdogs
2019-04-25 Fixed scrolling in console
2019-04-30 Added missing atollic projects
2019-04-30 Added forgotten patch checking tool
2019-04-30 Fixed diode polarity
2019-04-30 Updated hmi atollic project
2019-04-30 Increased stack size for hmi (compiled without optimizations)
2019-05-01 Added lcd params setup
2019-05-01 Inverted brake logic
2019-05-01 Check debug mode explicitly
2019-05-01 Fixed data type in rfm driver
2019-05-01 Added receiving code
2019-05-02 Fixed average speed infinite after mode change
2019-05-02 Set default value to piston len when rot encoder died
2019-05-02 Modified valve control to match physical wiring
2019-05-02 Removed magic code
2019-05-02 Disable rf mode for now
2019-05-02 Updated valve control - back valves are inverted as it was easier to update code than rewire the connector
2019-05-04 Fixed opamp on ecu board to one with correct power range
2019-05-04 Reduced resistors for horn and brake buttons to switch on mosfets
2019-05-04 Save current mode only for non debug modes
2019-05-06 Fixed tabs on select calling
2019-05-06 Control error led from console warn status
2019-05-07 Fixed interrupt stack size for ecu
2019-05-07 Fixed inputs reading, workarounded horn button
2019-05-07 Reboot if assert fails (only the current thread hangs, others are still running)
2019-05-07 Cleaned up tabs
2019-05-07 Updated rf module format to match the python side
2019-05-08 Fixed closing valves
2019-05-08 Enabled RF module in hmi
2019-05-08 Initialize spi before rf module
2019-05-08 Build with sys module (reboot)
2019-05-09 Fixed opening serial port from telemetry
2019-05-09 Fixed uart in telemetry module
2019-05-09 Don't interrupt the cycle on brake press
2019-05-10 Added blinking upon data receiving
2019-05-10 Fixed unpacking telemetry data
2019-05-10 Updated gui default values
2019-05-12 Added final specs
2019-05-12 Added TODO
2019-05-12 Added readme
2019-06-18 Added images to readme
